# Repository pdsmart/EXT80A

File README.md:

# EXT80A - External Expansion Card Adapter for the MZ-80A
This project outlines the design of an adapter which allows the Sharp MZ-80A to be used with a single expansion card. 

Normally an MZ-80A would require the MZ-80AEU expansion unit to add expansion cards but these units are not freely available.

The adapter can be seen here: https://twitter.com/engineerswork1/status/1641513915925291013

Either submit the latest release zip package in releases/ directory to a PCB fabrication plant or contact me as I may have spare.

My website, https://eaw.app will have full build instructions in due course.

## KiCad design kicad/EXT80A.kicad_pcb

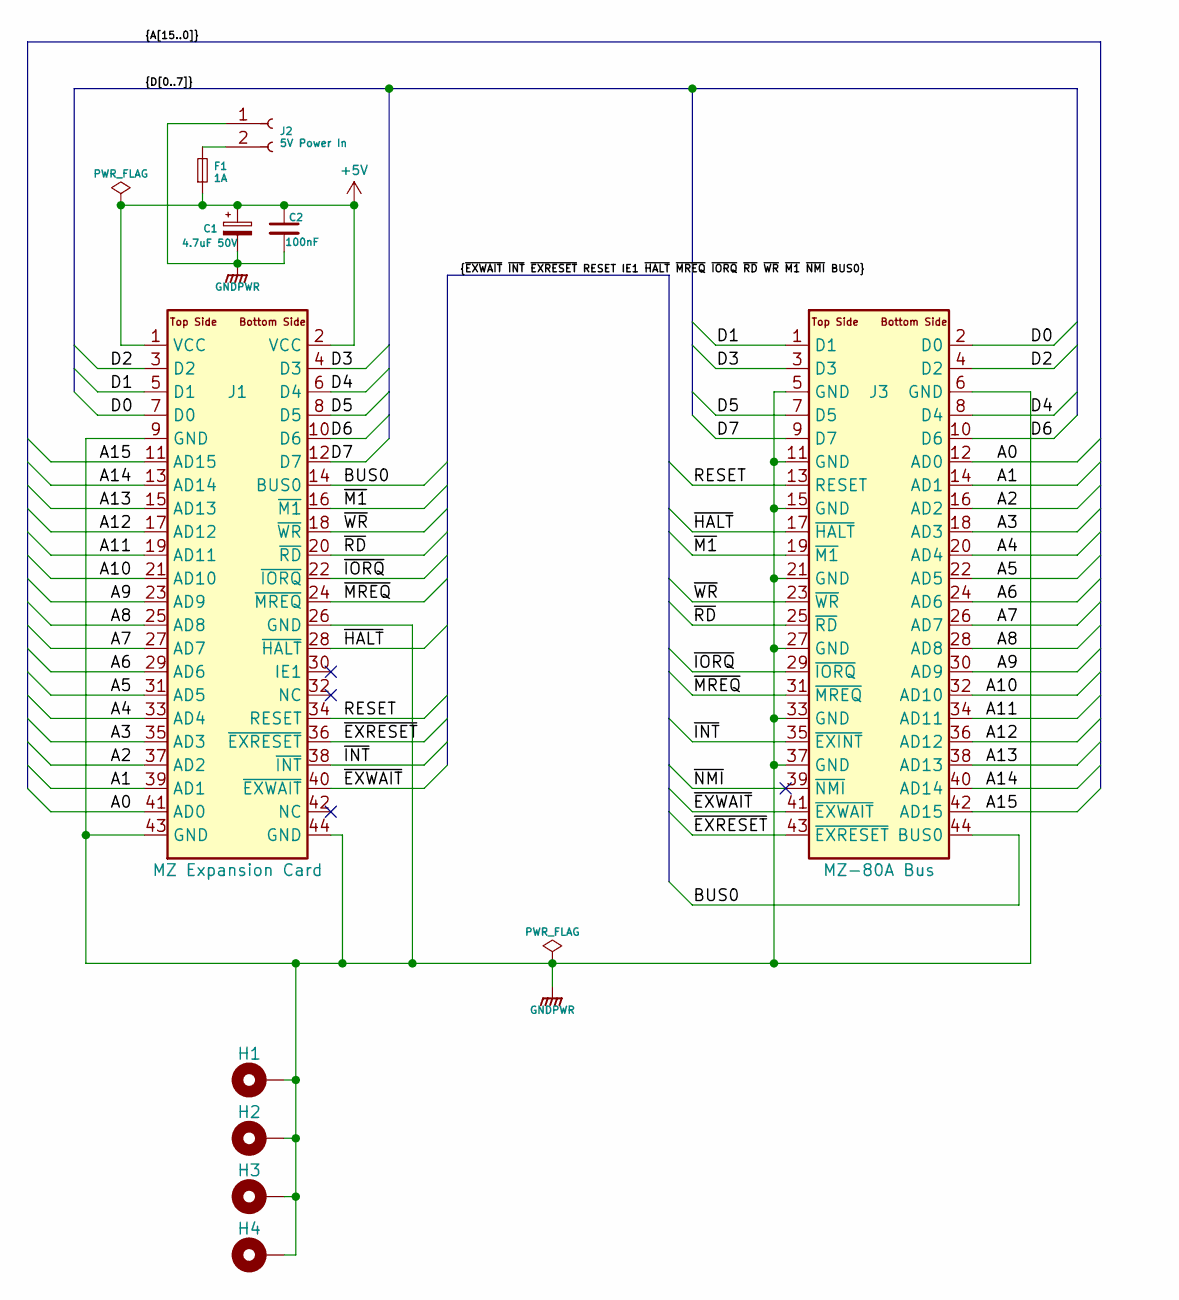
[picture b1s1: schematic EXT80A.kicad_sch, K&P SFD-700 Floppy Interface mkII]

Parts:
C1: 4.7uF 50V; CP_Radial_D4.0mm_P2.00mm
C2: 100nF; C_Disc_D5.0mm_W2.5mm_P2.50mm
F1: 1A; Fuse_1210_3225Metric_Pad1.42x2.65mm_HandSolder
H1, H2, H3, H4: MountingHole_Pad; MountingHole_3.2mm_M3_Pad_Via
J1: MZ Expansion Card; EdgeCardConnector_2_54mm_44way
J2: 5V Power In; JST_XH_B2B-XH-AM_1x02_P2.50mm_Vertical
J3: MZ-80A Bus; EdgeCardConnector_2_54mm_44way

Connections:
+5V: C1.1, C2.1, F1.1, J1.1 (VCC), J1.2 (VCC)
/A0: J1.41 (AD0), J3.12 (AD0)
/A1: J1.39 (AD1), J3.14 (AD1)
/A2: J1.37 (AD2), J3.16 (AD2)
/A3: J1.35 (AD3), J3.18 (AD3)
/A4: J1.33 (AD4), J3.20 (AD4)
/A5: J1.31 (AD5), J3.22 (AD5)
/A6: J1.29 (AD6), J3.24 (AD6)
/A7: J1.27 (AD7), J3.26 (AD7)
/A8: J1.25 (AD8), J3.28 (AD8)
/A9: J1.23 (AD9), J3.30 (AD9)
/A10: J1.21 (AD10), J3.32 (AD10)
/A11: J1.19 (AD11), J3.34 (AD11)
/A12: J1.17 (AD12), J3.36 (AD12)
/A13: J1.15 (AD13), J3.38 (AD13)
/A14: J1.13 (AD14), J3.40 (AD14)
/A15: J1.11 (AD15), J3.42 (AD15)
/BUS0: J1.14 (BUS0), J3.44 (BUS0)
/D0: J1.7 (D0), J3.2 (D0)
/D1: J1.5 (D1), J3.1 (D1)
/D2: J1.3 (D2), J3.4 (D2)
/D3: J1.4 (D3), J3.3 (D3)
/D4: J1.6 (D4), J3.8 (D4)
/D5: J1.8 (D5), J3.7 (D5)
/D6: J1.10 (D6), J3.10 (D6)
/D7: J1.12 (D7), J3.9 (D7)
/RESET: J1.34 (RESET), J3.13 (RESET)
/~EXRESET: J1.36 (~EXRESET), J3.43 (~EXRESET)
/~EXWAIT: J1.40 (~EXWAIT), J3.41 (~EXWAIT)
/~HALT: J1.28 (~HALT), J3.17 (~HALT)
/~INT: J1.38 (~INT), J3.35 (~EXINT)
/~IORQ: J1.22 (~IORQ), J3.29 (~IORQ)
/~M1: J1.16 (~M1), J3.19 (~M1)
/~MREQ: J1.24 (~MREQ), J3.31 (~MREQ)
/~NMI: J3.39 (~NMI)
/~RD: J1.20 (~RD), J3.25 (~RD)
/~WR: J1.18 (~WR), J3.23 (~WR)
GNDPWR: C1.2, C2.2, H1.1, H2.1, H3.1, H4.1, J1.9 (GND), J1.26 (GND), J1.43 (GND), J1.44 (GND), J2.1, J3.5 (GND), J3.6 (GND), J3.11 (GND), J3.15 (GND), J3.21 (GND), J3.27 (GND), J3.33 (GND), J3.37 (GND)
unnamed: F1.2, J2.2

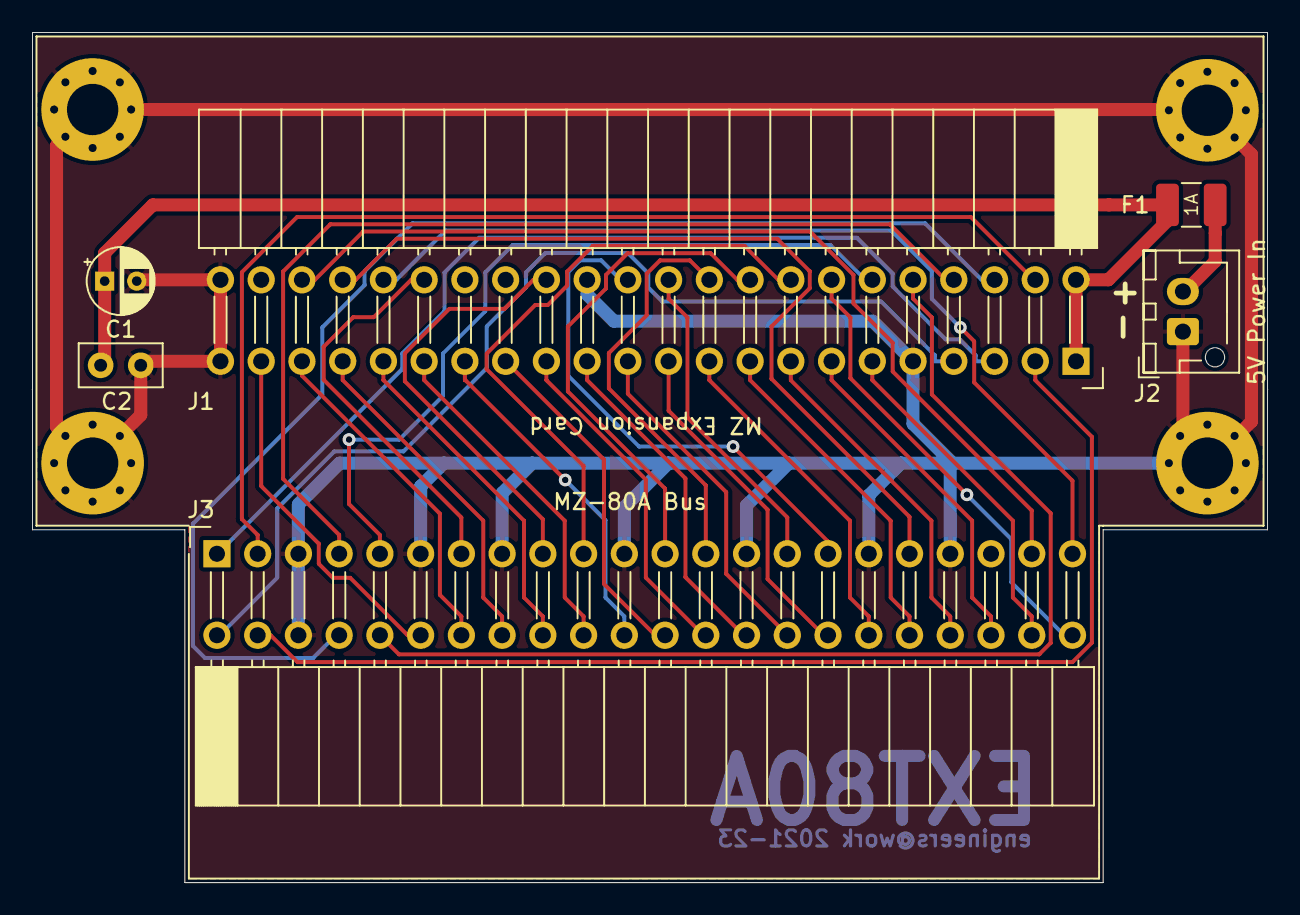
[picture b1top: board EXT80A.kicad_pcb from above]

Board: 2 copper layers, 77.0 x 53.0 mm, 10 parts (0 on the bottom side), 38 nets.

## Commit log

2023-04-18 Repo setup
2023-04-18 First release
